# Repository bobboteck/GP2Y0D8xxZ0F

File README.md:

# GP2Y0D8xxZ0F
A board designed with KiCAD for Sharp sensor GP2Y0D805Z0F, GP2Y0D810Z0F and GP2Y0D815Z0F

I had bought some of these sensors with a friend, without taking them with boards that are easily found on the online store, because we had the need for stable fixing points, that these models did not guarantee.
Then we decided to create a board for PTH components, but on the way, thanks to some of KiCAD libraries and others that I have modified, I have designed the board so it could also be assembled with SMD components.

## The circuit diagram

How you can see on the schema, there are another difference with the commercial solution, the connector have four pin (the commercial product have only 3). The fourth pin is used to command the Enable pin of Sharp sensor, in this way you can activate the sensor only when you need to use it, and conseguently save power.
Typically the current consumption is between 6 and 10 mA, when the Enable pin is put to 0V consumption drops to 8uA. When the Enable pin is put to 5V, it takes about 2 mS to obtain a valid measurement.
On the board is present a solder Jumper (JP1), you can close it with solder to set the Enable always active, **but REMEBER not to use the connector Enable pin**.

## PCB design

How explained before, the PCB design was tinked not for a small possible size (approximately 24x27 mm), but to leave, to those who will have to mount it, the freedom to choose whether to use SMD or PTH components.
The following picture is a 3D render of PCB, not all component have a 3D module, but you can see the board design.

## Board support
I have designed a specific support for this card, to be printed with a 3D printer, to achieve a stable fixing of the sensor. You can see it on [Tinkercad](https://www.tinkercad.com/things/4nSgSBEPW0j).

***Warning!*** *Currently I have not yet done a 3D printing test*

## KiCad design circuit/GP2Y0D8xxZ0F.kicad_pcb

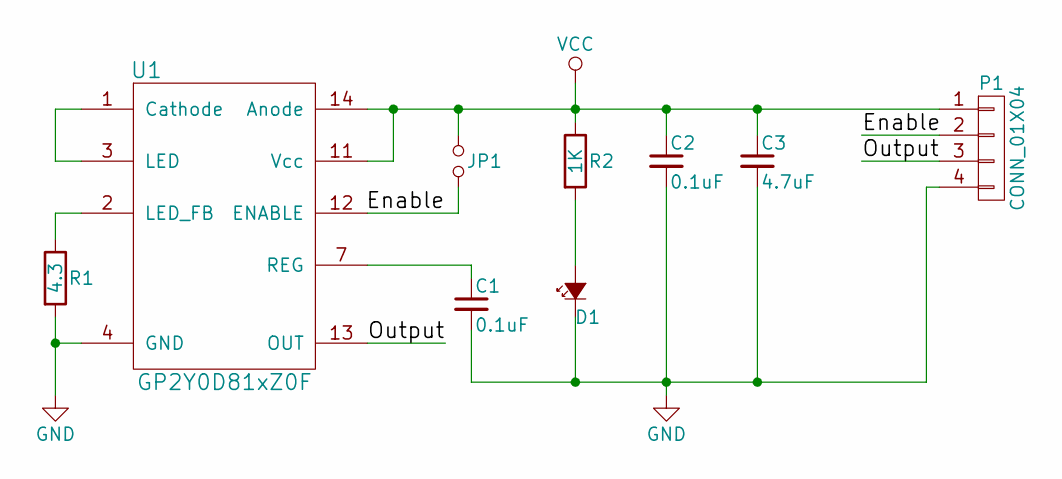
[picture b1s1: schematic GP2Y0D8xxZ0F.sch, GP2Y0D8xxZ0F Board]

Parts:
C1, C2: 0.1uF; C_1210_HandSoldering
C3: 4.7uF; C_1210_HandSoldering
D1: Led; LED_1206
JP1: Jumper_NO_Small; R_0603
P1: CONN_01X04; Pin_Header_Straight_1x04
R1: 4.3; Resistor_SMD+THTuniversal_0805to1206_RM10_HandSoldering
R2: 1K; Resistor_SMD+THTuniversal_0805to1206_RM10_HandSoldering
U1: GP2Y0D81xZ0F

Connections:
/Enable: JP1.2, P1.2, U1.12 (ENABLE)
/Output: P1.3, U1.13 (OUT)
GND: C1.2, C2.2, C3.2, D1.1 (K), P1.4, R1.2, U1.4 (GND)
unnamed: C1.1, U1.7 (REG)
unnamed: D1.2 (A), R2.2
unnamed: R1.1, U1.2 (LED_FB)
unnamed: U1.1 (Cathode), U1.3 (LED)
VCC: C2.1, C3.1, JP1.1, P1.1, R2.1, U1.11 (Vcc), U1.14 (Anode)

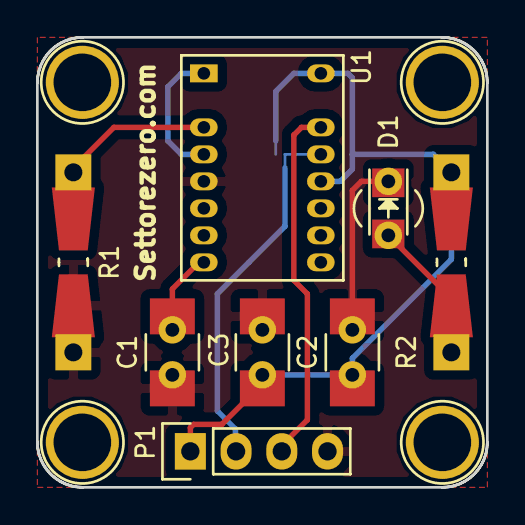
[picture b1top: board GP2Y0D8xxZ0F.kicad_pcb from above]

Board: 2 copper layers, 25.0 x 25.0 mm, 9 parts (1 on the bottom side), 8 nets.

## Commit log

2016-04-30 Added a picture
2016-04-30 Edit the readme file
2016-04-30 Moved solder Jumper for select Enable mode in Bottom Layer
2016-04-30 Modified trak with
2016-05-01 Varios editing of text
2018-05-26 Create LICENSE
2018-05-26 Modified project paths
2018-05-26 Added 3D WRML file end size on PCB design
2018-05-26 New folder for 3D file
2018-05-26 3D model of circuit support
2018-05-26 An image of 3D support
2018-05-26 Update readme file
2018-10-30 Generated Gerber and Drill files
2019-01-23 First convert try and resize
2019-01-23 changes in progress, open project with version 5 of kicad and the resizing started
2019-01-25 nothing
2019-02-04 New distribution of component in new size 25x25 mm
2020-10-09 Pcb resizing
2020-10-09 Completed resizing and redraw
2020-10-11 Generated gerber and drill file
2020-10-11 Modified and added same images
2020-10-11 Code example for Arduino
